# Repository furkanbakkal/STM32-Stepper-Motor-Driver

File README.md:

STM32-Stepper-Motor-Driver

-Hi! This project for Istanbul University Cerrahpaşa Electrical and Electronics Engineering graduation. 

-This is "STM32 and N-MOS Based Stepper Motor Driver"

- 2 layer PCB
- Full stepper motor control circuit

## Features

- Microstepping up to 1/258
- Very quiet and vibration-free step motor driving
- Current limiting
- High current support (up to 8A)
- Speed control (up to 10KHz pulse)
- Motor direction control (CW, CCW)

## Tech

- STM32F401RBT6
- IR2104 MOS gate driver

## Photos

Note: Cable jumps on the board have been fixed in version 1.2

## Demo

You can check this Google Drive link for real life demo: https://drive.google.com/file/d/10obyRq6SgMOz6bZmb6Qkc-JsMecKdY-S/view?usp=sharing

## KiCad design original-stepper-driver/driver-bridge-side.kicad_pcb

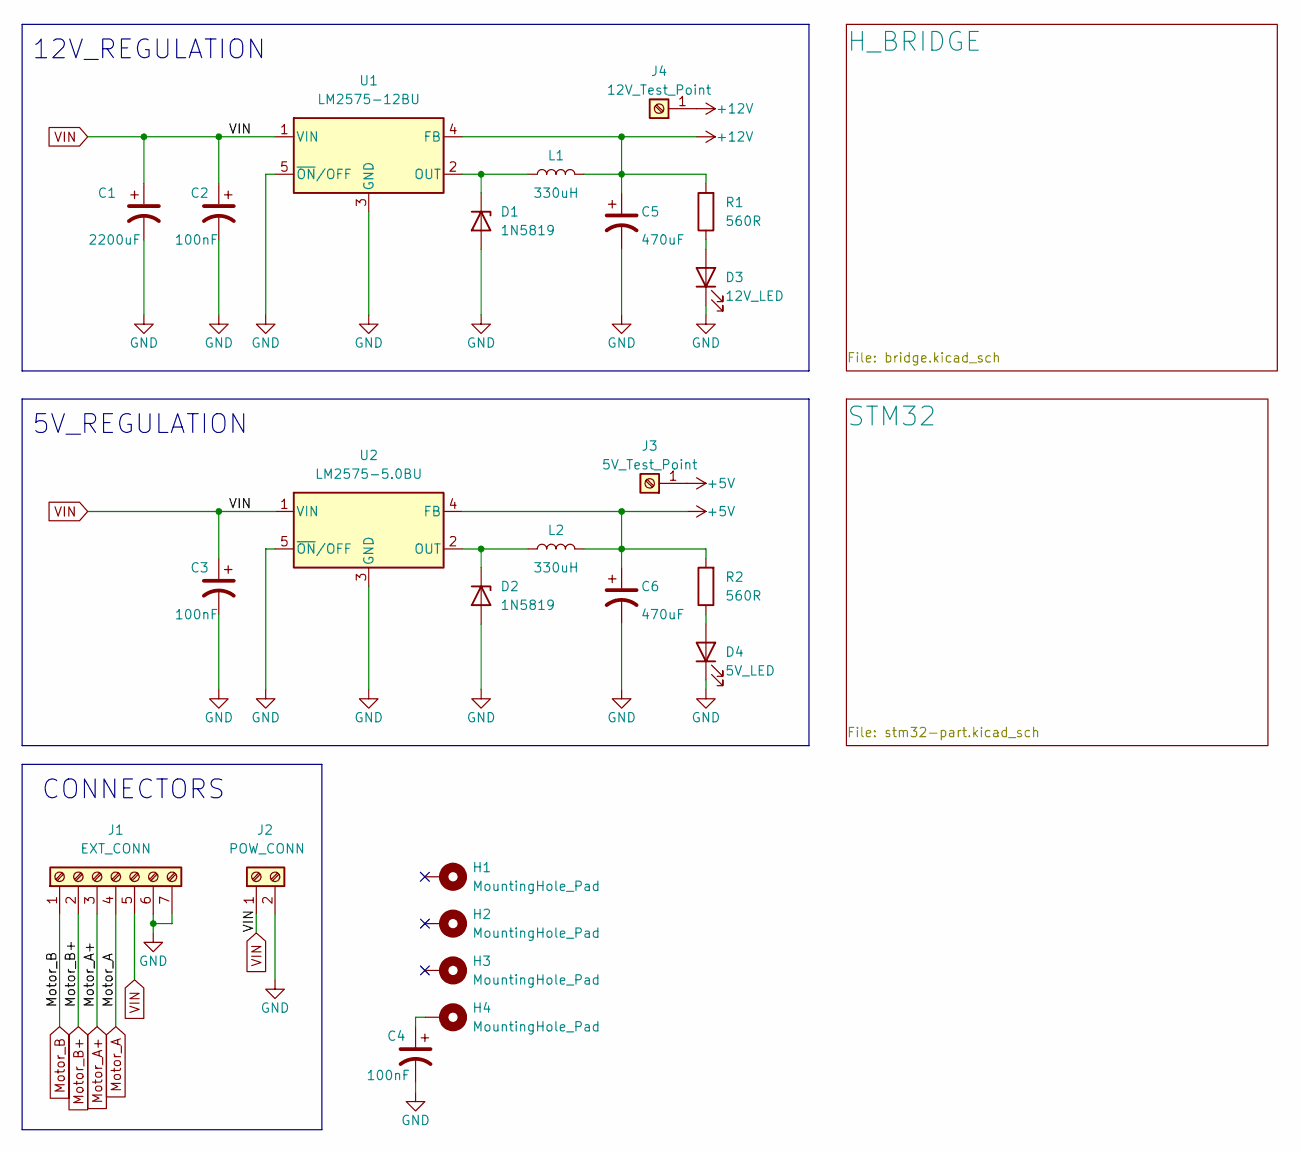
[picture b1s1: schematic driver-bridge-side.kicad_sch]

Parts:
C1: 2200uF; CP_Radial_D14.0mm_P7.50mm
C2, C3, C4: 100nF; C_0805_2012Metric_Pad1.18x1.45mm_HandSolder
C5, C6: 470uF; C_Elec_10x10.2
D1, D2: 1N5819; D_SOD-123
D3: 12V_LED; LED_0805_2012Metric_Pad1.15x1.40mm_HandSolder
D4: 5V_LED; LED_0805_2012Metric_Pad1.15x1.40mm_HandSolder
H1, H2, H3, H4: MountingHole_Pad; MountingHole_3.7mm_Pad_Via
J1: EXT_CONN; TerminalBlock_Phoenix_MKDS-1,5-7_1x07_P5.00mm_Horizontal
J2: POW_CONN; TerminalBlock_Phoenix_MKDS-1,5-2-5.08_1x02_P5.08mm_Horizont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
J3: 5V_Test_Point; TestPoint_Pad_D1.5mm
J4: 12V_Test_Point; TestPoint_Pad_D1.5mm
L1, L2: 330uH; L_Bourns_SRP1038C_10.0x10.0mm
R1, R2: 560R; R_0805_2012Metric_Pad1.20x1.40mm_HandSolder
U1: LM2575-12BU; TO-263-5_TabPin3
U2: LM2575-5.0BU; TO-263-5_TabPin3

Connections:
+5V: C6.1, J3.1, L2.2, R2.2, U2.4 (FB); also elsewhere on the board
+12V: C5.1, J4.1, L1.2, R1.2, U1.4 (FB); also elsewhere on the board
GND: C1.2, C2.2, C3.2, C4.2, C5.2, C6.2, D1.2 (A), D2.2 (A), D3.1 (K), D4.1 (K), J1.6, J1.7, J2.2, U1.3 (GND), U1.5 (~ON/OFF), U2.3 (GND), U2.5 (~ON/OFF); also elsewhere on the board
Motor_A: J1.4; also elsewhere on the board
Motor_A+: J1.3; also elsewhere on the board
Motor_B: J1.1; also elsewhere on the board
Motor_B+: J1.2; also elsewhere on the board
unnamed: C4.1, H4.1
unnamed: D1.1 (K), L1.1, U1.2 (OUT)
unnamed: D2.1 (K), L2.1, U2.2 (OUT)
unnamed: D3.2 (A), R1.1
unnamed: D4.2 (A), R2.1
VIN: C1.1, C2.1, C3.1, J1.5, J2.1, U1.1 (VIN), U2.1 (VIN); also elsewhere on the board

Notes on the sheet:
12V_REGULATION
5V_REGULATION
CONNECTORS

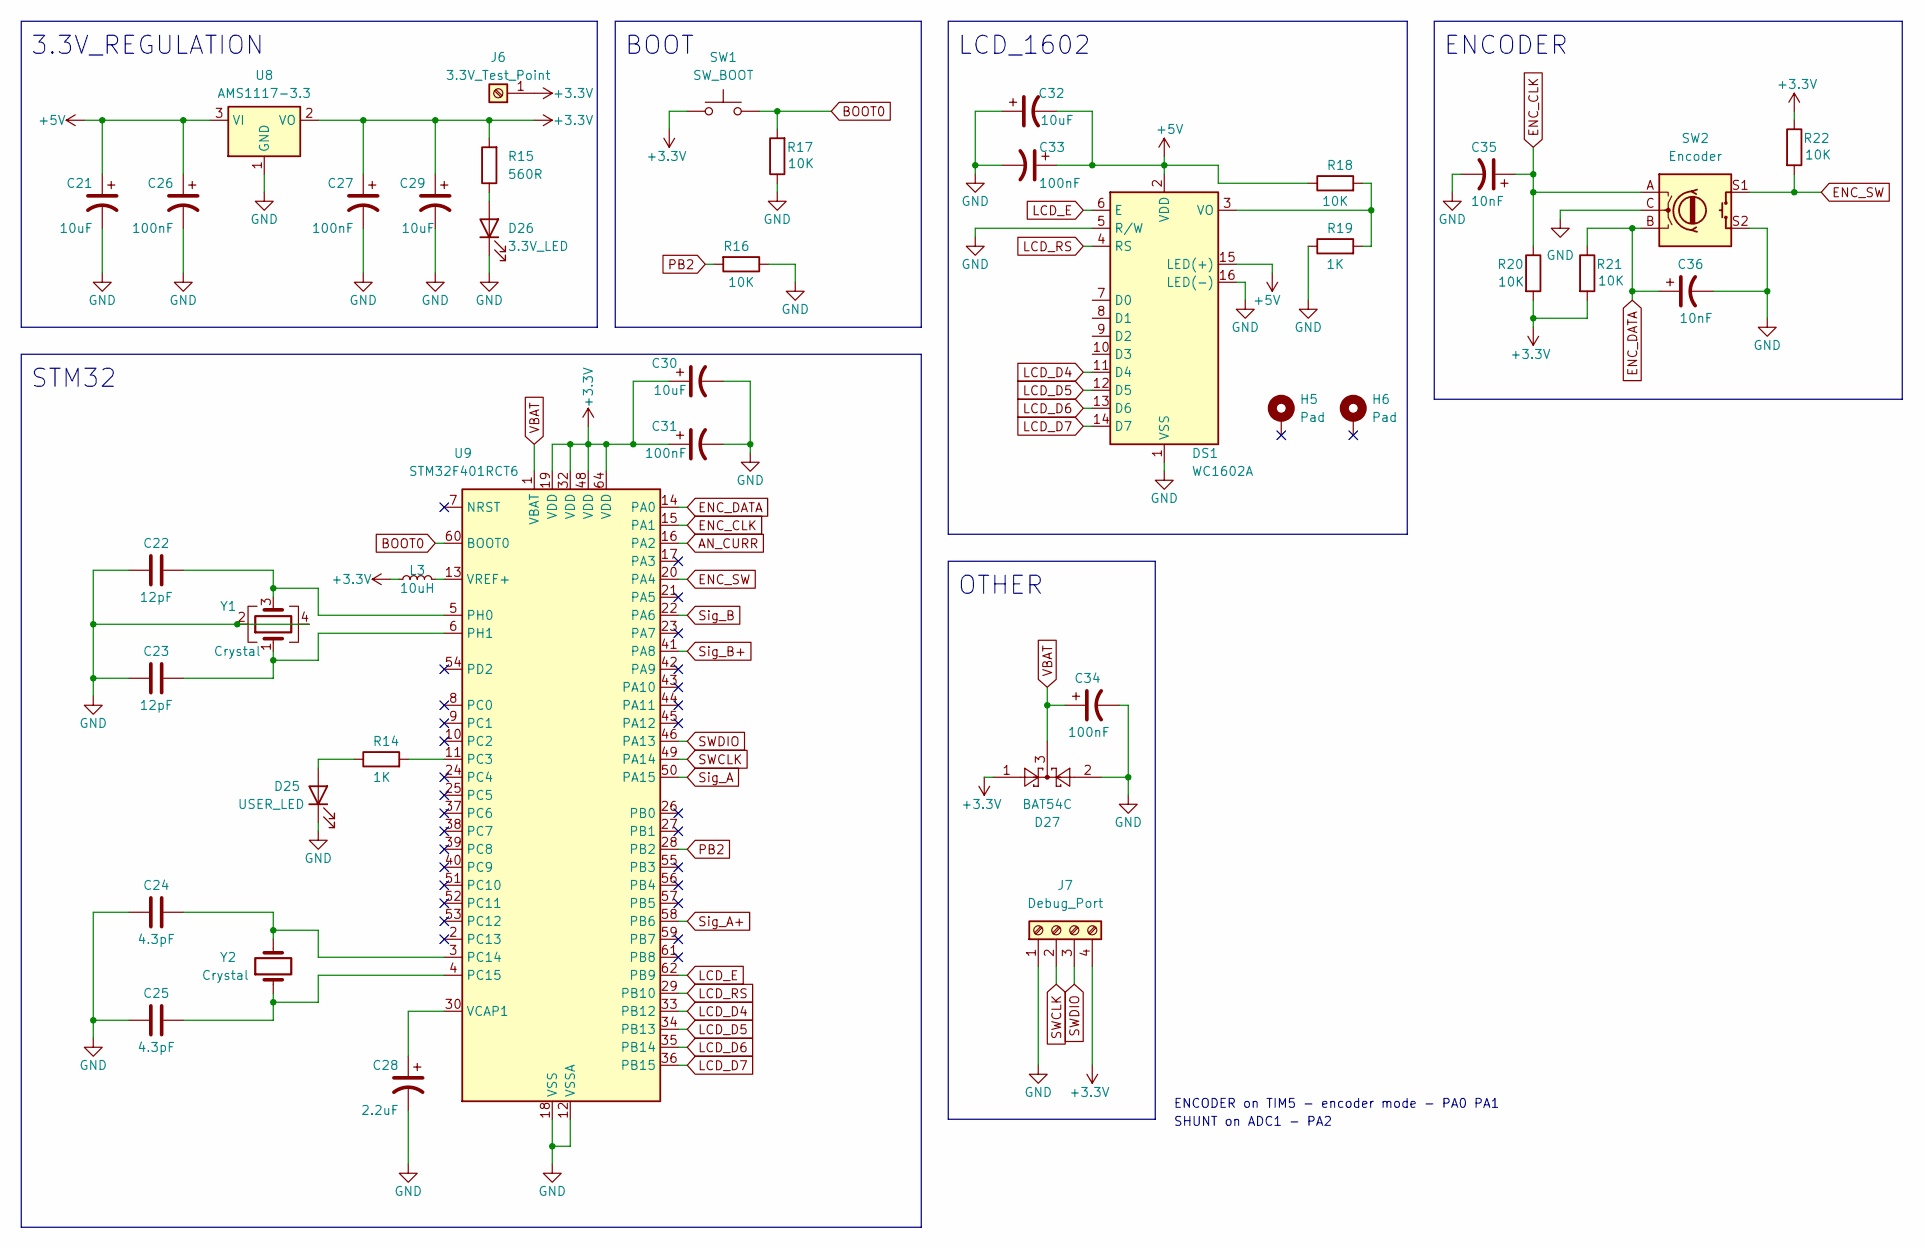
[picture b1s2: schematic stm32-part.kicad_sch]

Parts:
C21, C29, C30, C32: 10uF; C_0805_2012Metric_Pad1.18x1.45mm_HandSolder
C22, C23: 12pF; C_0201_0603Metric_Pad0.64x0.40mm_HandSolder
C24, C25: 4.3pF; C_0201_0603Metric_Pad0.64x0.40mm_HandSolder
C26, C27, C31, C33, C34: 100nF; C_0805_2012Metric_Pad1.18x1.45mm_HandSolder
C28: 2.2uF; C_0805_2012Metric_Pad1.18x1.45mm_HandSolder
C35, C36: 10nF; C_0805_2012Metric_Pad1.18x1.45mm_HandSolder
D25: USER_LED; LED_0805_2012Metric_Pad1.15x1.40mm_HandSolder
D26: 3.3V_LED; LED_0805_2012Metric_Pad1.15x1.40mm_HandSolder
D27: BAT54C; SOT-23
DS1: WC1602A
H5, H6: Pad; MountingHole_3.5mm_Pad
J6: 3.3V_Test_Point; TestPoint_Pad_D1.5mm
J7: Debug_Port; PinHeader_1x04_P2.54mm_Vertical
L3: 10uH; L_0805_2012Metric_Pad1.05x1.20mm_HandSolder
R14, R19: 1K; R_0805_2012Metric_Pad1.20x1.40mm_HandSolder
R15: 560R; R_0805_2012Metric_Pad1.20x1.40mm_HandSolder
R16, R17, R18, R20, R21, R22: 10K; R_0805_2012Metric_Pad1.20x1.40mm_HandSolder
SW1: SW_BOOT; SW_SPST_FSMSM
SW2: Encoder; RotaryEncoder_Alps_EC11E-Switch_Vertical_H20mm_NoChasis
U8: AMS1117-3.3; SOT-223-3_TabPin2
U9: STM32F401RCT6; LQFP-64_10x10mm_P0.5mm
Y1: Crystal; Crystal_SMD_3225-4Pin_3.2x2.5mm
Y2: Crystal; Crystal_SMD_3215-2Pin_3.2x1.5mm

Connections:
+3.3V: C27.1, C29.1, C30.1, C31.1, D27.1, J6.1, J7.4, L3.1, R15.2, R20.2, R21.2, R22.1, SW1.1, U8.2 (VO), U9.19 (VDD), U9.32 (VDD), U9.48 (VDD), U9.64 (VDD)
+5V: C21.1, C26.1, C32.2, C33.1, DS1.2 (VDD), DS1.15 (LED(+)), R18.1, U8.3 (VI); also elsewhere on the board
AN_CURR: U9.16 (PA2); also elsewhere on the board
BOOT0: R17.2, SW1.2, U9.60 (BOOT0)
ENC_CLK: C35.1, R20.1, SW2.A, U9.15 (PA1)
ENC_DATA: C36.1, R21.1, SW2.B, U9.14 (PA0)
ENC_SW: R22.2, SW2.S1, U9.20 (PA4)
GND: C21.2, C22.2, C23.1, C24.2, C25.1, C26.2, C27.2, C28.2, C29.2, C30.2, C31.2, C32.1, C33.2, C34.2, C35.2, C36.2, D25.1 (K), D26.1 (K), D27.2, DS1.1 (VSS), DS1.5 (R/W), DS1.16 (LED(-)), J7.1, R16.1, R17.1, R19.1, SW2.C, SW2.S2, U8.1 (GND), U9.12 (VSSA), U9.18 (VSS), U9.31 (VSS), U9.47 (VSS), U9.63 (VSS), Y1.2, Y1.4; also elsewhere on the board
LCD_D4: DS1.11 (D4), U9.33 (PB12)
LCD_D5: DS1.12 (D5), U9.34 (PB13)
LCD_D6: DS1.13 (D6), U9.35 (PB14)
LCD_D7: DS1.14 (D7), U9.36 (PB15)
LCD_E: DS1.6 (E), U9.62 (PB9)
LCD_RS: DS1.4 (RS), U9.29 (PB10)
unnamed: D25.2 (A), R14.1
unnamed: D26.2 (A), R15.1
unnamed: DS1.3 (VO), R18.2, R19.2
unnamed: R14.2, U9.11 (PC3)
unnamed: C24.1, U9.3 (PC14), Y2.2
unnamed: C25.2, U9.4 (PC15), Y2.1
unnamed: C22.1, U9.5 (PH0), Y1.3
unnamed: C23.2, U9.6 (PH1), Y1.1
unnamed: C28.1, U9.30 (VCAP1)
unnamed: L3.2, U9.13 (VREF+)
PB2: R16.2, U9.28 (PB2)
SWCLK: J7.2, U9.49 (PA14)
SWDIO: J7.3, U9.46 (PA13)
Sig_A: U9.50 (PA15); also elsewhere on the board
Sig_A+: U9.58 (PB6); also elsewhere on the board
Sig_B: U9.22 (PA6); also elsewhere on the board
Sig_B+: U9.41 (PA8); also elsewhere on the board
VBAT: C34.1, D27.3, U9.1 (VBAT)

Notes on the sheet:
STM32
LCD_1602
OTHER
BOOT
ENCODER on TIM5 - encoder mode - PA0 PA1
3.3V_REGULATION
SHUNT on ADC1 - PA2
ENCODER

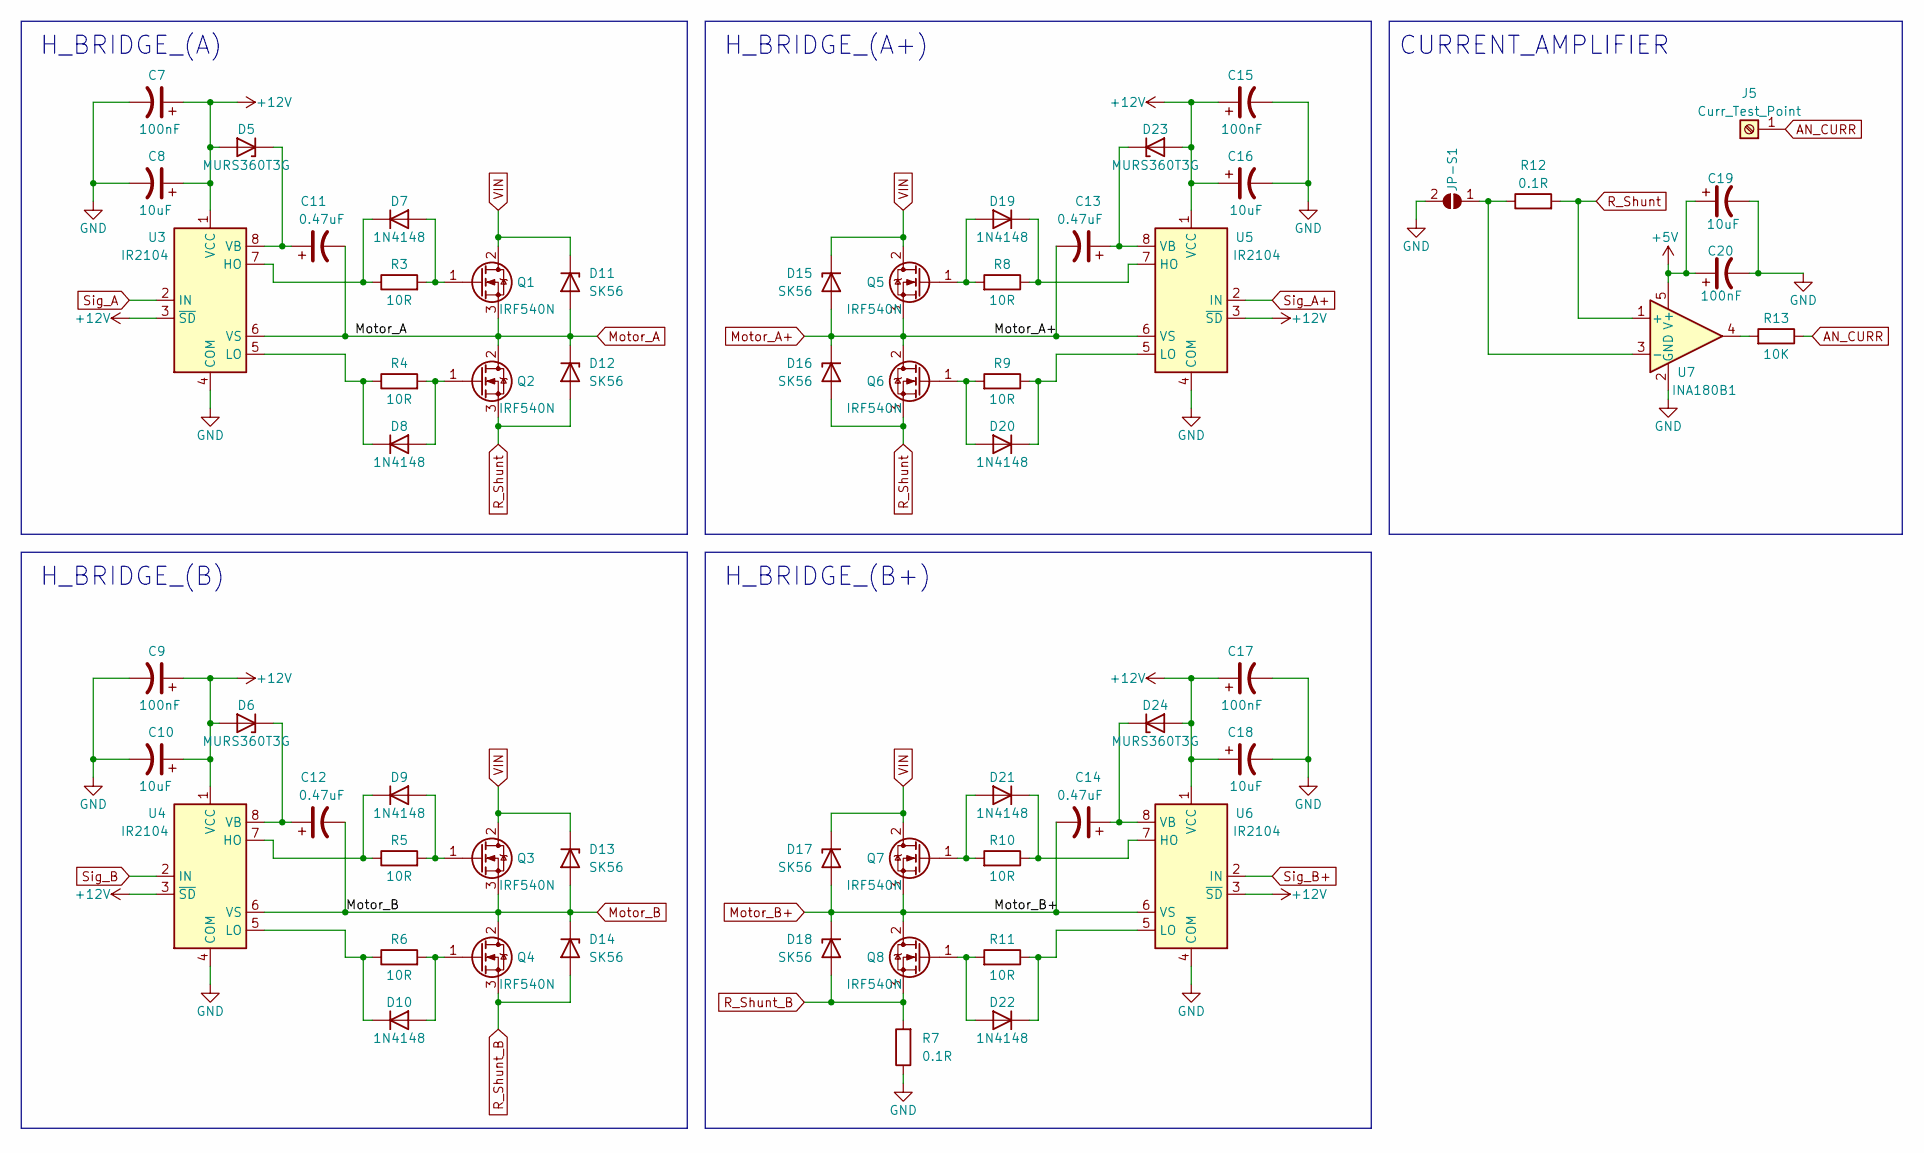
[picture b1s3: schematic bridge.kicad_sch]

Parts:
C7, C9, C15, C17, C20: 100nF; C_0805_2012Metric_Pad1.18x1.45mm_HandSolder
C8, C10, C16, C18, C19: 10uF; C_0805_2012Metric_Pad1.18x1.45mm_HandSolder
C11, C12, C13, C14: 0.47uF; CP_Radial_D4.0mm_P2.00mm
D5, D6, D23, D24: MURS360T3G; D_SMC
D7, D8, D9, D10, D19, D20, D21, D22: 1N4148; D_MiniMELF
D11, D12, D13, D14, D15, D16, D17, D18: SK56; D_SMC
J5: Curr_Test_Point; TestPoint_Pad_D1.5mm
JP-S1: SolderJumper_2_Open; SolderJumper-2_P1.3mm_Open_RoundedPad1.0x1.5mm
Q1, Q2, Q3, Q4, Q5, Q6, Q7, Q8: IRF540N; TO-252-2
R3, R4, R5, R6, R8, R9, R10, R11: 10R; R_0805_2012Metric_Pad1.20x1.40mm_HandSolder
R7, R12: 0.1R; R_2512_6332Metric_Pad1.40x3.35mm_HandSolder
R13: 10K; R_0805_2012Metric_Pad1.20x1.40mm_HandSolder
U3, U4, U5, U6: IR2104; SOIC-8_3.9x4.9mm_P1.27mm
U7: INA180B1; SOT-23-5_HandSoldering

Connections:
+5V: C19.1, C20.1, U7.5 (V+); also elsewhere on the board
+12V: C7.1, C8.1, C9.1, C10.1, C15.1, C16.1, C17.1, C18.1, D5.2 (A), D6.2 (A), D23.2 (A), D24.2 (A), U3.1 (VCC), U3.3 (~SD), U4.1 (VCC), U4.3 (~SD), U5.1 (VCC), U5.3 (~SD), U6.1 (VCC), U6.3 (~SD); also elsewhere on the board
AN_CURR: J5.1, R13.1; also elsewhere on the board
GND: C7.2, C8.2, C9.2, C10.2, C15.2, C16.2, C17.2, C18.2, C19.2, C20.2, JP-S1.2 (B), R7.1, U3.4 (COM), U4.4 (COM), U5.4 (COM), U6.4 (COM), U7.2 (GND); also elsewhere on the board
Motor_A: C11.2, D11.2 (A), D12.1 (K), Q1.3 (S), Q2.2 (D), U3.6 (VS); also elsewhere on the board
Motor_A+: C13.2, D15.2 (A), D16.1 (K), Q5.3 (S), Q6.2 (D), U5.6 (VS); also elsewhere on the board
Motor_B: C12.2, D13.2 (A), D14.1 (K), Q3.3 (S), Q4.2 (D), U4.6 (VS); also elsewhere on the board
Motor_B+: C14.2, D17.2 (A), D18.1 (K), Q7.3 (S), Q8.2 (D), U6.6 (VS); also elsewhere on the board
unnamed: C11.1, D5.1 (K), U3.8 (VB)
unnamed: C12.1, D6.1 (K), U4.8 (VB)
unnamed: D7.2 (A), Q1.1 (G), R3.2
unnamed: D7.1 (K), R3.1, U3.7 (HO)
unnamed: D8.2 (A), Q2.1 (G), R4.2
unnamed: D8.1 (K), R4.1, U3.5 (LO)
unnamed: D9.2 (A), Q3.1 (G), R5.2
unnamed: D9.1 (K), R5.1, U4.7 (HO)
unnamed: D10.2 (A), Q4.1 (G), R6.2
unnamed: D10.1 (K), R6.1, U4.5 (LO)
unnamed: D19.2 (A), Q5.1 (G), R8.2
unnamed: D19.1 (K), R8.1, U5.7 (HO)
unnamed: D20.2 (A), Q6.1 (G), R9.2
unnamed: D20.1 (K), R9.1, U5.5 (LO)
unnamed: D21.2 (A), Q7.1 (G), R10.2
unnamed: D21.1 (K), R10.1, U6.7 (HO)
unnamed: D22.2 (A), Q8.1 (G), R11.2
unnamed: D22.1 (K), R11.1, U6.5 (LO)
unnamed: C13.1, D23.1 (K), U5.8 (VB)
unnamed: C14.1, D24.1 (K), U6.8 (VB)
unnamed: JP-S1.1 (A), R12.1, U7.3 (-)
unnamed: R13.2, U7.4
R_Shunt: D12.2 (A), D16.2 (A), Q2.3 (S), Q6.3 (S), R12.2, U7.1 (+)
R_Shunt_B: D14.2 (A), D18.2 (A), Q4.3 (S), Q8.3 (S), R7.2
Sig_A: U3.2 (IN); also elsewhere on the board
Sig_A+: U5.2 (IN); also elsewhere on the board
Sig_B: U4.2 (IN); also elsewhere on the board
Sig_B+: U6.2 (IN); also elsewhere on the board
VIN: D11.1 (K), D13.1 (K), D15.1 (K), D17.1 (K), Q1.2 (D), Q3.2 (D), Q5.2 (D), Q7.2 (D); also elsewhere on the board

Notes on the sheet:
H_BRIDGE_(B)
H_BRIDGE_(A+)
H_BRIDGE_(A)
H_BRIDGE_(B+)
CURRENT_AMPLIFIER

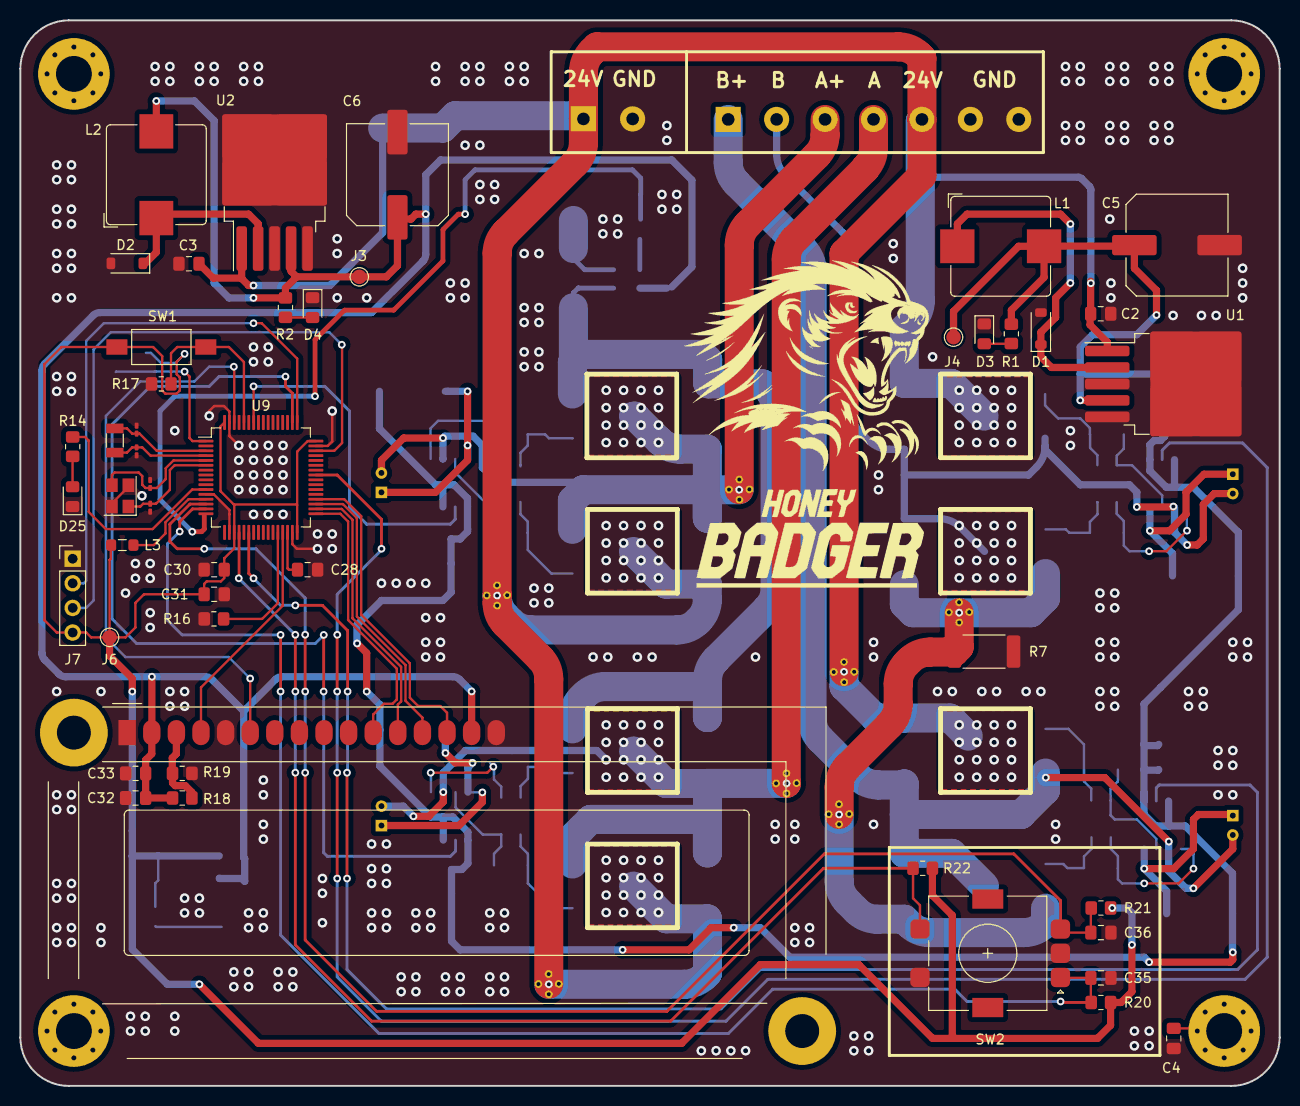
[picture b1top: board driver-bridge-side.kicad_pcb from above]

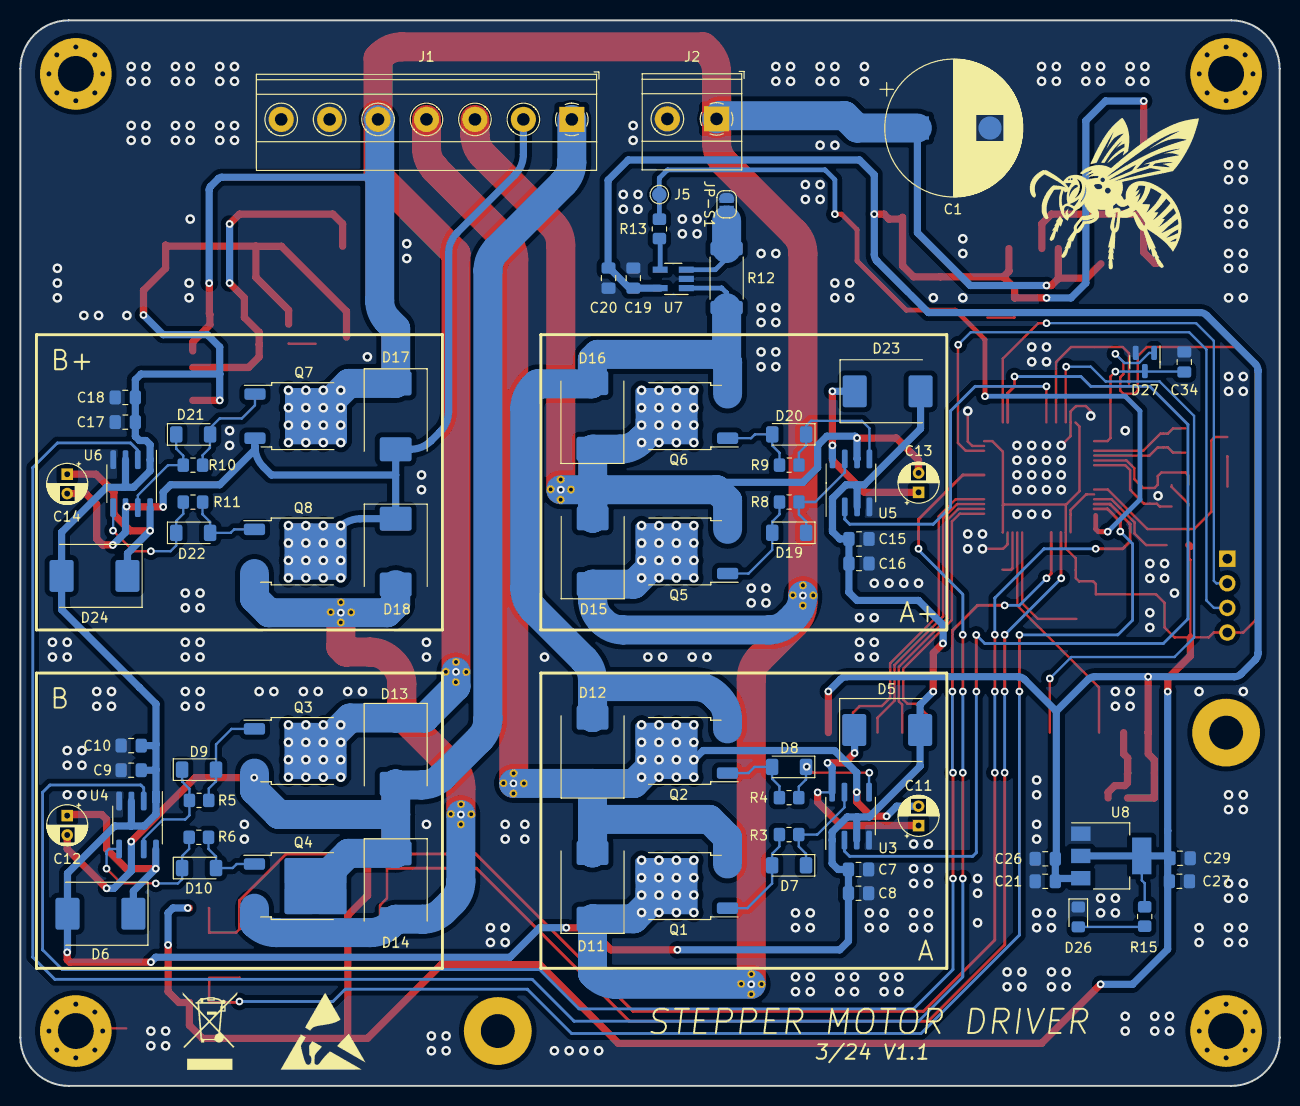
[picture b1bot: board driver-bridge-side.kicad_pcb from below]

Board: 2 copper layers, 130.0 x 110.0 mm, 128 parts (71 on the bottom side), 67 nets.

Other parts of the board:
V: (no value)
V#2, V#3, V#4: (no value)

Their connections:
Motor_A: V.1, V#2.1, V#3.1, V#4.1; also elsewhere on the board

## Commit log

2024-06-18 gerber file
2024-06-18 kicad files
2024-06-18 STM32 codes
2024-06-18 schematic as PDF
2024-06-18 PCB layout and 3D render
2024-06-28 stm32 code
